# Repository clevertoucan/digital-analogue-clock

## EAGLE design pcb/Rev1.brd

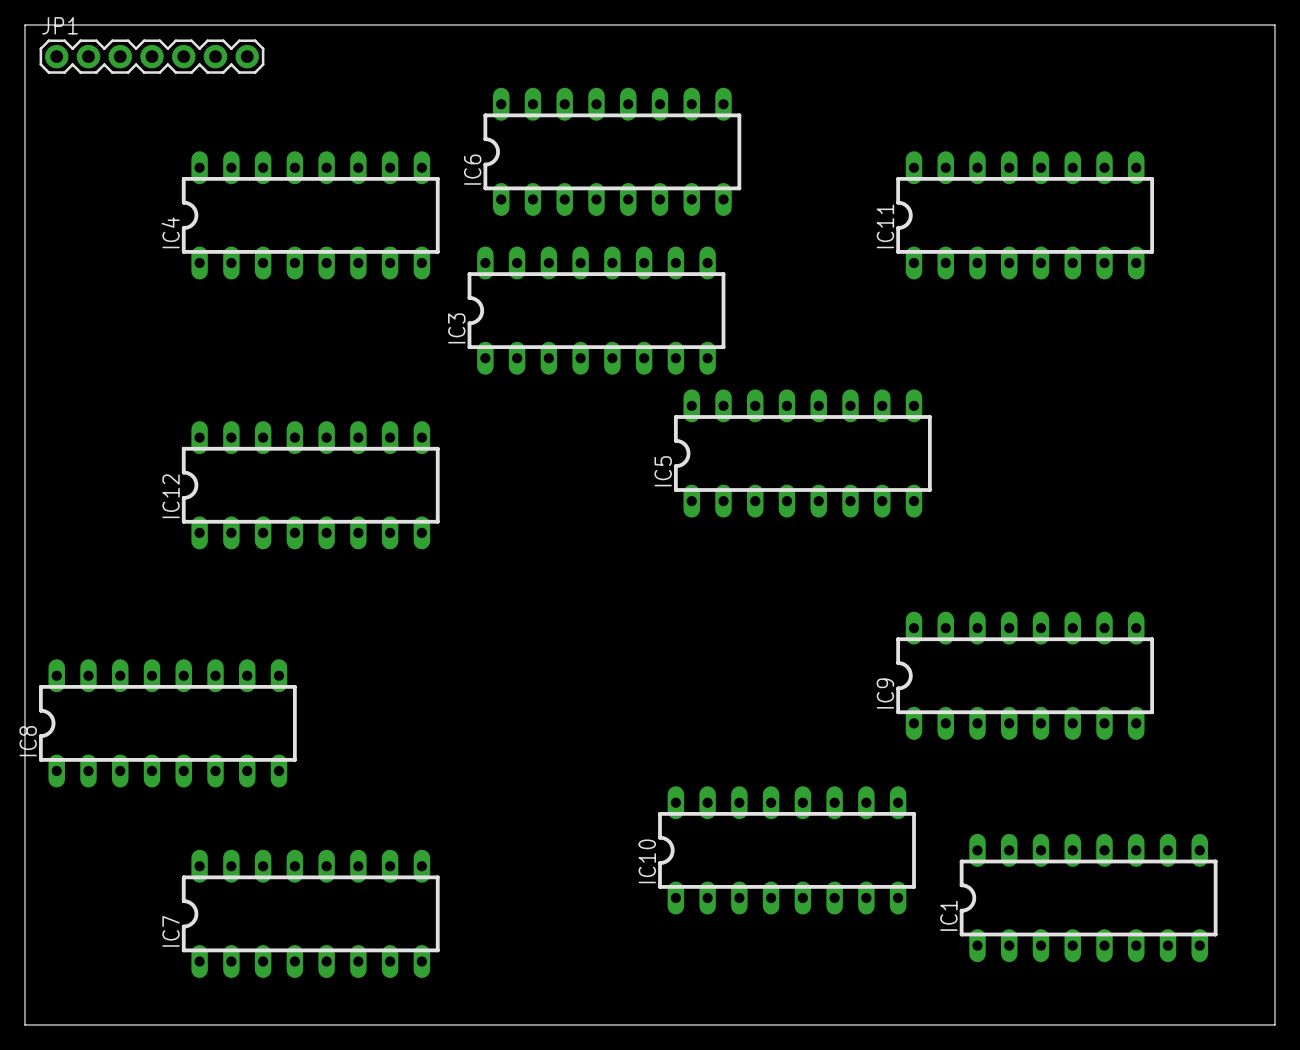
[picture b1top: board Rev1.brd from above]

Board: 2 copper layers, 100.0 x 80.0 mm, 12 parts (0 on the bottom side), 11 nets, no tracks yet.

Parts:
IC1, IC3, IC4, IC5, IC6, IC7, IC8, IC9, IC10, IC11, IC12: 74LS595N; DIL16
JP1: 1X07

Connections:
GND: IC1.8, IC3.8, IC4.8, IC5.8, IC8.8, IC11.8, IC12.8
GROUND: IC1.13, IC3.13, IC4.13, IC5.13, IC6.8, IC6.13, IC7.8, IC7.13, IC8.13, IC9.8, IC9.13, IC10.8, IC10.13, IC11.13, IC12.13, JP1.6
LATCH: IC1.12, IC4.12, IC6.12, IC7.12, IC8.12, IC9.12, IC10.12, IC11.12, IC12.12, JP1.5
unnamed: IC12.14, JP1.4
unnamed: IC11.14, IC12.9
unnamed: IC5.14, IC10.9
unnamed: IC1.14, IC5.9
unnamed: IC4.9, IC6.14
unnamed: IC8.9, IC9.14
unnamed: IC4.11, IC7.11, IC11.11, JP1.3
VCC: IC1.16, IC3.16, IC4.10, IC4.16, IC5.10, IC5.16, IC6.16, IC7.10, IC7.16, IC8.10, IC8.16, IC9.16, IC10.16, IC11.10, IC11.16, IC12.16, JP1.7

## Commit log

2015-01-21 All files
    Includes schematics, code, and a basic graphic representation. The
    program that runs on the Arduino is DaisyChain.ino in /Code/DaisyChain
2015-01-21 Blah
    Bleh
2015-01-21 ew,khvgasdh
    asdlkfjhaslkfgjhadflkgj
2015-01-21 POWERPOINTS!
2015-01-28 <djfhasliughadilfughasdf

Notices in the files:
parts and their libraries:
SparkFun-DigitalIC: Licensing: Creative Commons ShareAlike 4.0 International - https://creativecommons.org/licenses/by-sa/4.0
